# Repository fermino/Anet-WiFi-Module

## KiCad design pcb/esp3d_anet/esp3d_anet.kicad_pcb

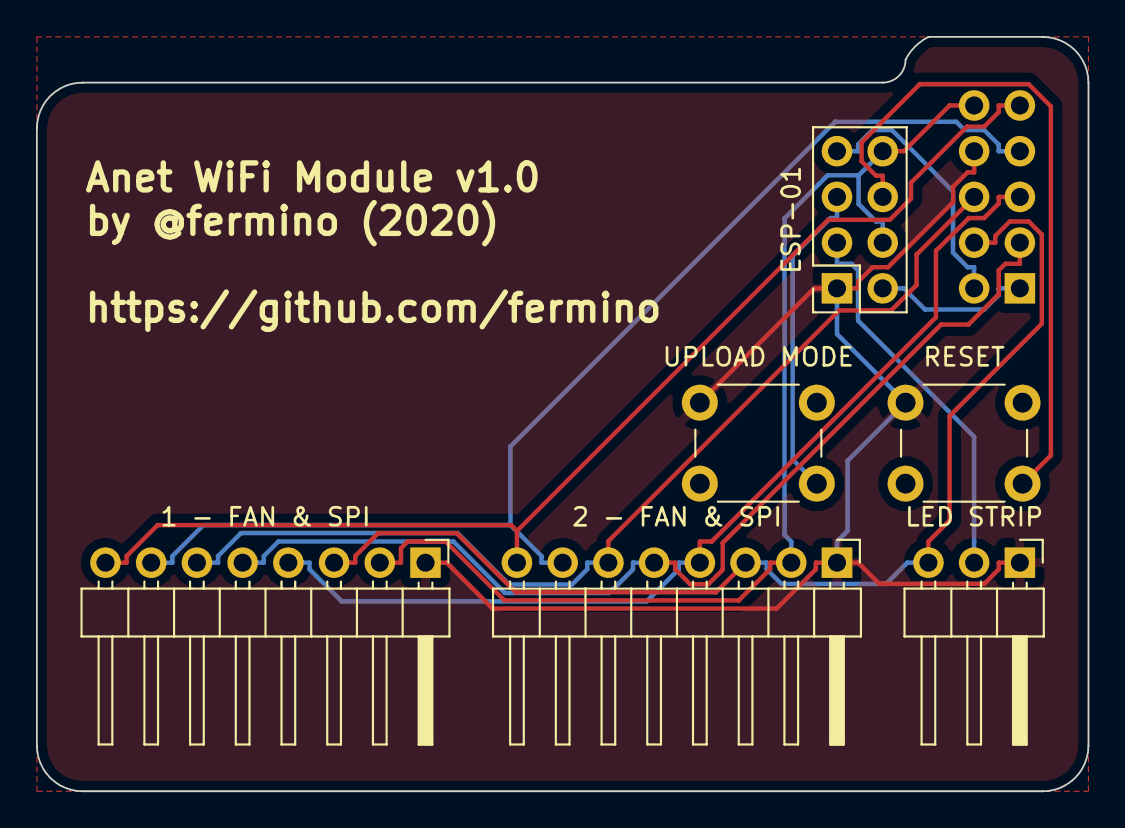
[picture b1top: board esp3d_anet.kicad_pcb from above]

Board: 2 copper layers, 58.4 x 41.9 mm, 7 parts (1 on the bottom side), 13 nets.

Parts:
1 - FAN & SPI, 2 - FAN & SPI: Conn_01x08; PinHeader_1x08_P2.54mm_Horizontal
3D PRINTER: Conn_02x05_Odd_Even; PinSocket_2x05_P2.54mm_Vertical
ESP-01: Conn_02x04_Odd_Even; PinSocket_2x04_P2.54mm_Vertical
LED STRIP: Conn_01x03; PinHeader_1x03_P2.54mm_Horizontal
RESET: SW_Push; SW_PUSH_6mm_Opposite
UPLOAD MODE: SW_Push; SW_PUSH_6mm_Opposite

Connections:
3D_FAN: 1 - FAN & SPI.8, 2 - FAN & SPI.8, 3D PRINTER.9
3D_MISO: 1 - FAN & SPI.5, 2 - FAN & SPI.5, 3D PRINTER.3
3D_MOSI: 1 - FAN & SPI.6, 2 - FAN & SPI.6, 3D PRINTER.6
3D_RESET: 1 - FAN & SPI.7, 2 - FAN & SPI.7, 3D PRINTER.7
3D_SCK: 1 - FAN & SPI.4, 2 - FAN & SPI.4, 3D PRINTER.5
3V3: 1 - FAN & SPI.2, 2 - FAN & SPI.2, 3D PRINTER.10, ESP-01.4, ESP-01.8
5V: 1 - FAN & SPI.3, 2 - FAN & SPI.3, 3D PRINTER.4, LED STRIP.3
BOOT_MODE: ESP-01.5, UPLOAD MODE.2
ESP_RX: 3D PRINTER.2, ESP-01.7
ESP_TX: 3D PRINTER.1, ESP-01.2
GND: 1 - FAN & SPI.1, 2 - FAN & SPI.1, 3D PRINTER.8, ESP-01.1, LED STRIP.1, RESET.1, UPLOAD MODE.1
LED_OUT: ESP-01.3, LED STRIP.2
RESET: ESP-01.6, RESET.2

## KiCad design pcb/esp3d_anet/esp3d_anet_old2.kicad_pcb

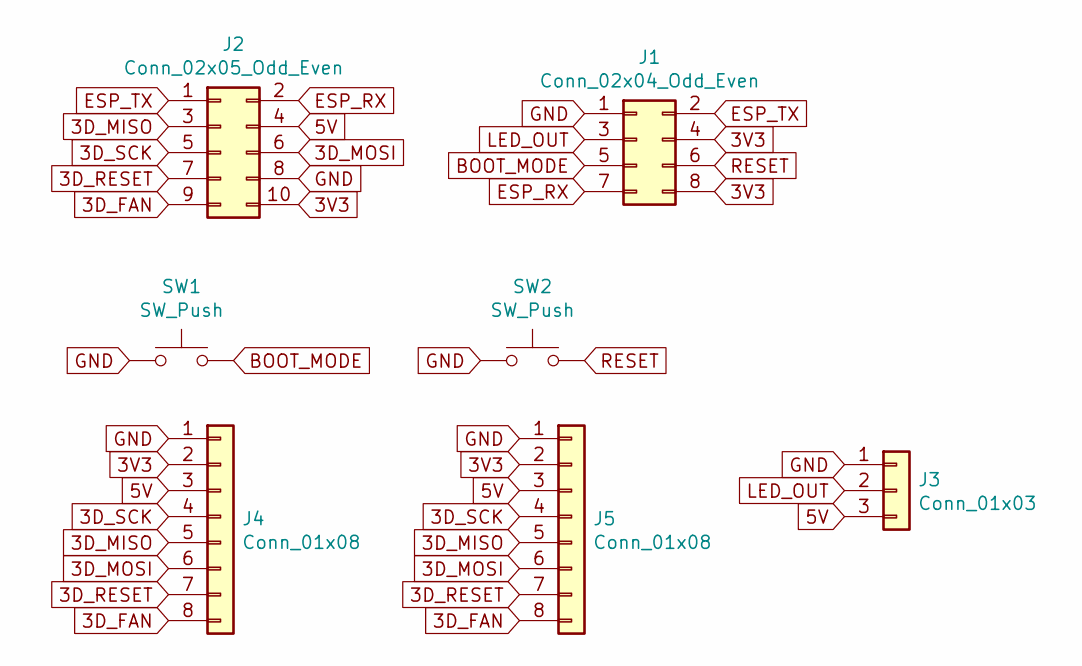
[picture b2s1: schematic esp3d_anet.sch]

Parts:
J1: Conn_02x04_Odd_Even; PinSocket_2x04_P2.54mm_Vertical
J2: Conn_02x05_Odd_Even; PinSocket_2x05_P2.54mm_Vertical
J3: Conn_01x03; PinHeader_1x03_P2.54mm_Horizontal
J4, J5: Conn_01x08; PinHeader_1x08_P2.54mm_Horizontal
SW1, SW2: SW_Push; SW_PUSH_6mm_Opposite

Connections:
3D_FAN: J2.9, J4.8, J5.8
3D_MISO: J2.3, J4.5, J5.5
3D_MOSI: J2.6, J4.6, J5.6
3D_RESET: J2.7, J4.7, J5.7
3D_SCK: J2.5, J4.4, J5.4
3V3: J1.4, J1.8, J2.10, J4.2, J5.2
5V: J2.4, J3.3, J4.3, J5.3
BOOT_MODE: J1.5, SW1.2
ESP_RX: J1.7, J2.2
ESP_TX: J1.2, J2.1
GND: J1.1, J2.8, J3.1, J4.1, J5.1, SW1.1, SW2.1
LED_OUT: J1.3, J3.2
RESET: J1.6, SW2.2

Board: 2 copper layers, 7 parts (1 on the bottom side), 13 nets, no tracks yet.

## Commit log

2020-10-09 First working board :)
2020-10-09 güeno :c
